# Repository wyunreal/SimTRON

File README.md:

# SimTRON

MultiSim SMS device !

This repo contains source code and hardware specifications for building a 8 SIMs communications device to monitor SMS reception on up to 8 mobile lines.

# Hardware

The device is based on an Arduino PRO mini, running at 16 MHz and 5V. Board designed using Eagle Cad, sources under **hardware** folder.

## Schematic:

## Board:

## Connections:

- **PSW:** power switch, connect the ATX power switch.
- **RSW:** reset switch, connect the ATX reset switch.
- **ATXE:** ATX enable signal, connect, from left to right: ATX Black (GND), ATX Green (Enable)
- **LPWR:** Logic power: connect, from left to right: ATX Purple (5V SB), ATX Black (GND)
- **GSMPWR:** GSM modules [1 to 4] power: connect, from left to right: ATX Red (5V), ATX Black (GND)
- **GSMPWR2:** GSM modules [5 to 8] power: connect, from left to right: Any alternative 5V poser supply (can be ATX Yellow (12V) through a 5V DC-DC step down, ATX Black (GND)
-- Take into account that you don't need to connect this power connector if you closes the JP1 jumper. In this case, all GSM modules will be powered through GSMPWR connector.
- **GSM[1..8]:** gsm modules, take into account polarity, reset pin on GSM module marked as 7 in board.

## List of materials

| Name | link | Unit price | Quantity | Total price |
|------|------|------------|----------|-------------|
| IC 74HC4051 | https://www.amazon.es/cd74hc4051e-Analog-Channel-CKT-16-Ti/dp/B01JV6VPJ8/ref=sr_1_fkmr1_1?ie=UTF8&qid=1528913467&sr=8-1-fkmr1&keywords=analog+mux+4051 | 3.50 € | 1 | 3.50 € |
| GPRS SIm800L Modem | https://www.amazon.es/Sharplace-SIM800L-Tarjeta-Cuatribanda-QUAD-BAND/dp/B075D9ZYPW/ref=sr_1_16?ie=UTF8&qid=1528789781&sr=8-16&keywords=sim800l | 12.99 € | 8 | 103.92 € |
| Arduino Pro Mini 328P | https://www.amazon.es/Arduino-ATMEGA328-Avr328P-desarrollo-development/dp/B01DLPAAAK/ref=sr_1_2?ie=UTF8&qid=1528790069&sr=8-2&keywords=arduino+pro+mini | 5 € | 1 | 5 € |
| FTDI USB Adapter | https://www.amazon.es/tinxi%C2%AE-FT232RL-adaptador-convertidor-Arduino/dp/B01C2P9GD2/ref=sr_1_8?s=electronics&ie=UTF8&qid=1528790180&sr=1-8&keywords=ftdi+usb | 5.99 € | 1 | 5.99 € |
| Mini USB to Micro USB cable | https://www.amazon.es/Extensi%C3%B3n-Adaptador-Dispositivo-Charger-Converter/dp/B01MEDCEBJ/ref=sr_1_6?s=electronics&ie=UTF8&qid=1528911416&sr=1-6&keywords=mini+usb+to+micro+usb | 7.99 € | 1 | 7.99 € |
| Raspberry PI Zero W Starter kit | https://www.amazon.es/PiHut-Zero-Essentials-Kit-Raspberry/dp/B06XCYGP27/ref=sr_1_5?ie=UTF8&qid=1528790276&sr=8-5&keywords=raspberry+pi+zero+w | 25 € | 1 | 25 € |
| Micro ATX enclosure | https://www.amazon.es/gp/product/B00TKP0E34/ref=oh_aui_detailpage_o01_s00?ie=UTF8&psc=1 | 46.95 € | 1 | 46.95 € |
| Manufactoring at China | https://www.pcbway.com/ | 10 € | 1 | 10 € |

Total price: 208.35 €

## Printed parts

This part has been designed to support the 8 Bnc antennas, fitting in any ATX case back side. You can print it with any 3D printer.

# Firmware

The firmware is under the **firmware** folder, you can use Arduino IDE to mod or add new features.

## Interface

The firmware uses **Serial** interface to communicate with host computer, the commands follows a simple text protocol, one command on each line and with following structure:

`commandOpCode param1 param2 param3`

Commands response are valid JSON objects.

### Available commands:

**Status command:**

`status channelNo`

Param: int, GSM channel number, 0 to 7

Response:

```javascript
{
  "type": "status",
  "channel": int, // the channel: 0 to 7
  "power": "string", // whether the ATX power is "on" or "off"
  "isEnabled": int, // whether the channel is enabled (1) or not (0)
  "icc": "string", // full ICC of the sim, if not sim inserted, empty icc will be returned
  "msisdn": "string", // full msisdn of the sim, if no sim inserted, empty msisdn will be returned, also, if unknown msisd, a question mark will be returned "?"
  "networkStatus": int, // 1 to 10, indicating the GSM network status of the channel
  "status": "string" // descriptive and printable message for networkStatus
}
```

**Catalog command:**

`catalog`

Response:

8 status objects, one per GSM channel (see status command)

**Enable command:**

`enable channelNo`

Param: int, GSM channel number, 0 to 7

Response:

Same response than status command.

**Disable command:**

`disable channelNo`

Param: int, GSM channel number, 0 to 7

Response:

Same response than status command.

**Send SMS command:**

`sendSms channelNo destinationMsisdn "SMS text"`

Params:
- int channelNo: GSM channel number, 0 to 7, this channel will be used as sender.
- string senderMsisdn: MSISDN to send to.
- string smsText: short text to send as SMS (max 130 chars)

Response:

if SMS sent correctly:

```javascript
{
  "type": "info",
  "body": "SMS sent"
}
```

if not:

```javascript
{
  "type": "error",
  "body": "Error sending SMS"
}
```

**Reset command:**

`reset`

Response:

No response, the system will reset and boot messages will be shown.

**Support command:**

`support`

Response:

```javascript
{
  "type": "support",
  "body": "Simtron v1.0.0 get support at https://github.com/wyunreal/simtron"
}
```

## Push messages

The device can send messages to the host computer without the needding of a command, these messages are:

**Boot started:**

```javascript
{
  "type": "booting",
  "body": "Booting Up ..."
}
```

**Boot completed:**

```javascript
{
  "type": "booting",
  "body": "System ready ..."
}
```

**SMS Received:**

```javascript
{
  "type": "sms",
  "channel": int, // the channel: 0 to 7, receiver of the SMS
  "icc": "string", // full ICC of the sim receiving the SMS
  "msisdn": "string", // full msisdn of the sim receiving the SMS, if unknown msisd, a question mark will be returned "?"
  "sender": "string", // sender MSISDN;
  "datetime": "string", // a date and time string, ready for presentation
  "body": "string" // SMS text
}
```

## Burning the firmware to Arduino Pro Mini

As the firmware enables the Watch Dog Timer, in order to being able using an Arduino Pro Mini, you need to burn the Arduino UNO bootloader first, this is completely safe as Arduino Pro Mini is a tiny but full featured version of the Arduino UNO.

Follow these instructions to burn the bootloader using another arduino as programmer:

https://www.luisllamas.es/usar-arduino-para-reprogramar-el-bootloader/

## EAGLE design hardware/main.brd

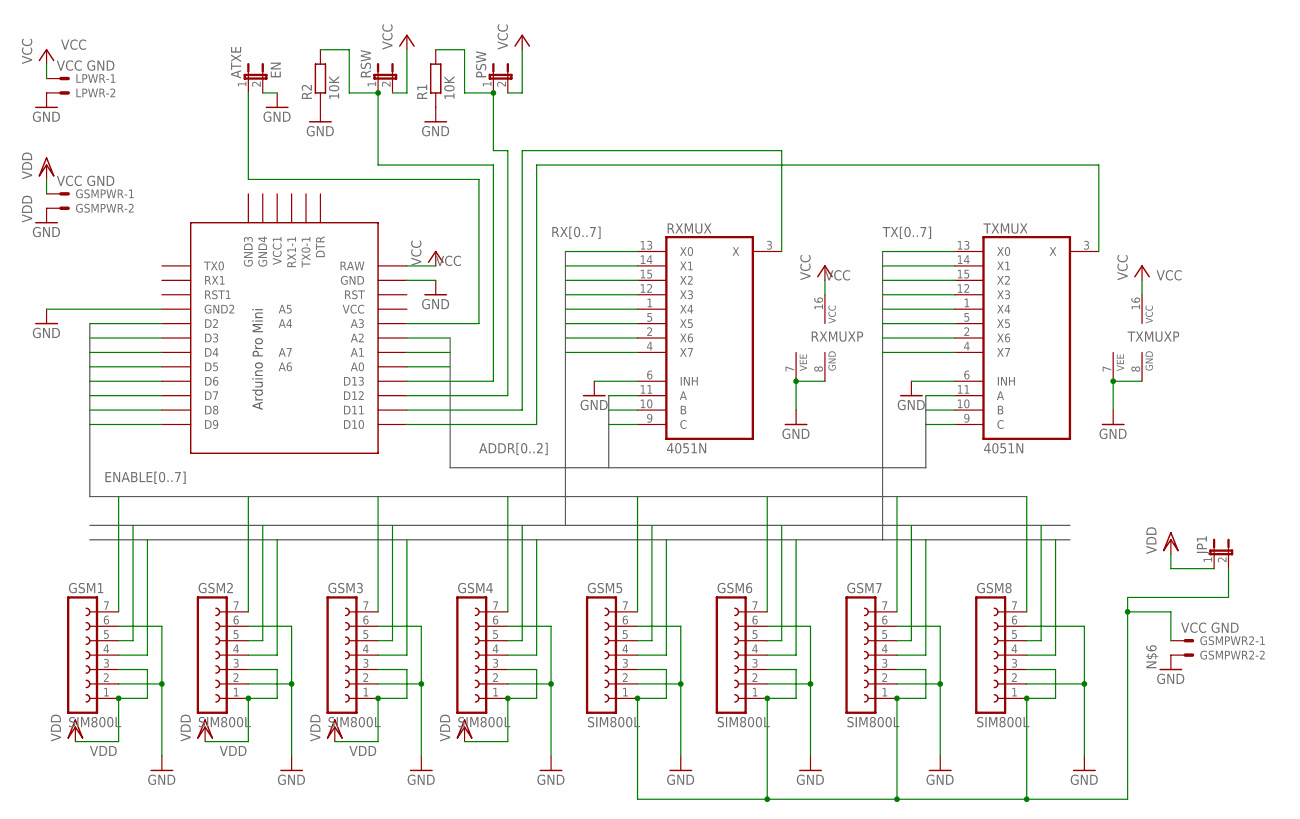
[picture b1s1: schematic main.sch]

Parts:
ARDUINO: PRO-MINI; PRO-MINI-2
ATXE: EN; JP1
GSM1, GSM2, GSM3, GSM4, GSM5, GSM6, GSM7, GSM8: SIM800L; FE07
GSMPWR, GSMPWR2: VCC GND; 22-23-2021
JP1: JP1
LPWR: VCC GND; 22-23-2021
PSW: JP1
R1, R2: 10K; 0204/7
RSW: JP1
RXMUX: 4051N; DIL16
TXMUX: 4051N; DIL16

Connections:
ADDR0: ARDUINO.A2, RXMUX.11 (A), TXMUX.11 (A)
ADDR1: ARDUINO.A1, RXMUX.10 (B), TXMUX.10 (B)
ADDR2: ARDUINO.A0, RXMUX.9 (C), TXMUX.9 (C)
ENABLE0: ARDUINO.D2, GSM1.7
ENABLE1: ARDUINO.D3, GSM2.7
ENABLE2: ARDUINO.D4, GSM3.7
ENABLE3: ARDUINO.D5, GSM4.7
ENABLE4: ARDUINO.D6, GSM5.7
ENABLE5: ARDUINO.D7, GSM6.7
ENABLE6: ARDUINO.D8, GSM7.7
ENABLE7: ARDUINO.D9, GSM8.7
GND: ARDUINO.GND, ARDUINO.GND1 (GND2), ATXE.2, GSM1.2, GSM1.6, GSM2.2, GSM2.6, GSM3.2, GSM3.6, GSM4.2, GSM4.6, GSM5.2, GSM5.6, GSM6.2, GSM6.6, GSM7.2, GSM7.6, GSM8.2, GSM8.6, GSMPWR.2, GSMPWR2.2, LPWR.2, R1.1, R2.1, RXMUX.6 (INH), RXMUX.7 (VEE), RXMUX.8 (GND), TXMUX.6 (INH), TXMUX.7 (VEE), TXMUX.8 (GND)
unnamed: ARDUINO.D11, RXMUX.3 (X)
unnamed: ARDUINO.D10, TXMUX.3 (X)
unnamed: ARDUINO.D13, R2.2, RSW.1
unnamed: GSM5.1, GSM5.3, GSM6.1, GSM6.3, GSM7.1, GSM7.3, GSM8.1, GSM8.3, GSMPWR2.1, JP1.2
unnamed: ARDUINO.A3, ATXE.1
unnamed: ARDUINO.D12, PSW.1, R1.2
RX0: GSM1.5, RXMUX.13 (X0)
RX1: GSM2.5, RXMUX.14 (X1)
RX2: GSM3.5, RXMUX.15 (X2)
RX3: GSM4.5, RXMUX.12 (X3)
RX4: GSM5.5, RXMUX.1 (X4)
RX5: GSM6.5, RXMUX.5 (X5)
RX6: GSM7.5, RXMUX.2 (X6)
RX7: GSM8.5, RXMUX.4 (X7)
TX0: GSM1.4, TXMUX.13 (X0)
TX1: GSM2.4, TXMUX.14 (X1)
TX2: GSM3.4, TXMUX.15 (X2)
TX3: GSM4.4, TXMUX.12 (X3)
TX4: GSM5.4, TXMUX.1 (X4)
TX5: GSM6.4, TXMUX.5 (X5)
TX6: GSM7.4, TXMUX.2 (X6)
TX7: GSM8.4, TXMUX.4 (X7)
VCC: ARDUINO.RAW, LPWR.1, PSW.2, RSW.2, RXMUX.16 (VCC), TXMUX.16 (VCC)
VDD: GSM1.1, GSM1.3, GSM2.1, GSM2.3, GSM3.1, GSM3.3, GSM4.1, GSM4.3, GSMPWR.1, JP1.1

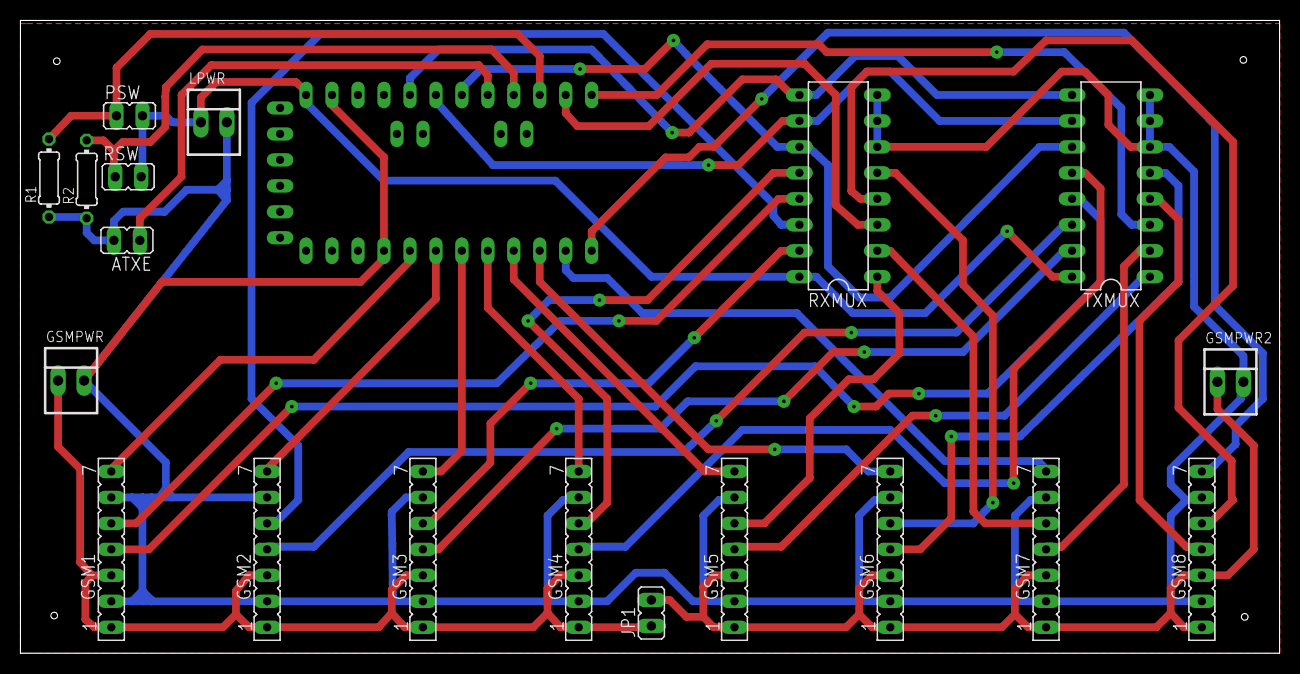
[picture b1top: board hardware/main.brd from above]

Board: 2 copper layers, 123.2 x 61.9 mm, 20 parts (0 on the bottom side), 36 nets.

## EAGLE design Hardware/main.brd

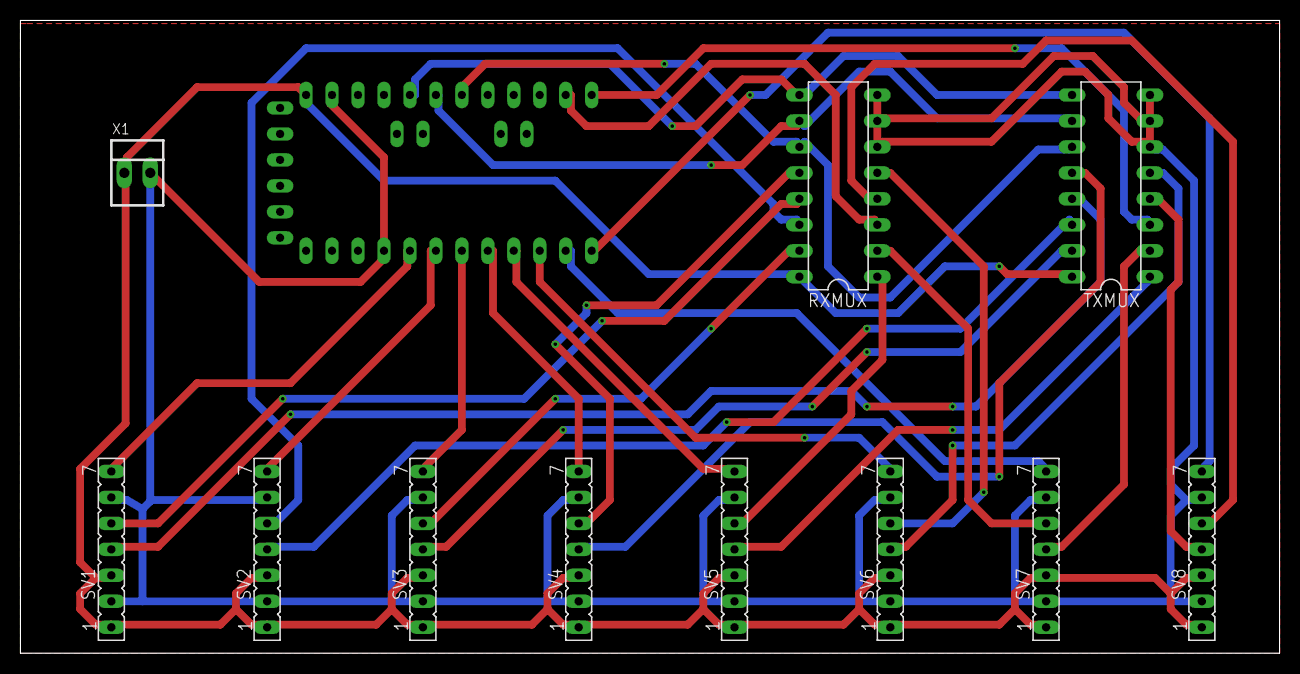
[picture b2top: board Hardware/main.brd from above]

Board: 2 copper layers, 123.2 x 61.9 mm, 12 parts (0 on the bottom side), 32 nets.

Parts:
RXMUX: 4051N; DIL16
SV1, SV2, SV3, SV4, SV5, SV6, SV7, SV8: FE07
TXMUX: 4051N; DIL16
U$1: PRO-MINI-2
X1: 22-23-2021

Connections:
ADDR0: RXMUX.11, TXMUX.11, U$1.A2
ADDR1: RXMUX.10, TXMUX.10, U$1.A1
ADDR2: RXMUX.9, TXMUX.9, U$1.A0
ENABLE0: SV1.7, U$1.D2
ENABLE1: SV2.7, U$1.D3
ENABLE2: SV3.7, U$1.D4
ENABLE3: SV4.7, U$1.D5
ENABLE4: SV5.7, U$1.D6
ENABLE5: SV6.7, U$1.D7
ENABLE6: SV7.7, U$1.D8
ENABLE7: SV8.7, U$1.D9
GND: RXMUX.6, RXMUX.8, SV1.2, SV1.6, SV2.2, SV2.6, SV3.2, SV3.6, SV4.2, SV4.6, SV5.2, SV5.6, SV6.2, SV6.6, SV7.2, SV7.6, SV8.2, SV8.6, TXMUX.6, TXMUX.8, U$1.GND, U$1.GND1, X1.2
unnamed: RXMUX.3, U$1.D11
unnamed: TXMUX.3, U$1.D10
RX0: RXMUX.13, SV1.5
RX1: RXMUX.14, SV2.5
RX2: RXMUX.15, SV3.5
RX3: RXMUX.12, SV4.5
RX4: RXMUX.1, SV5.5
RX5: RXMUX.5, SV6.5
RX6: RXMUX.2, SV7.5
RX7: RXMUX.4, SV8.5
TX0: SV1.4, TXMUX.13
TX1: SV2.4, TXMUX.14
TX2: SV3.4, TXMUX.15
TX3: SV4.4, TXMUX.12
TX4: SV5.4, TXMUX.1
TX5: SV6.4, TXMUX.5
TX6: SV7.4, TXMUX.2
TX7: SV8.4, TXMUX.4
VCC: RXMUX.16, SV1.1, SV1.3, SV2.1, SV2.3, SV3.1, SV3.3, SV4.1, SV4.3, SV5.1, SV5.3, SV6.1, SV6.3, SV7.1, SV7.3, SV8.1, SV8.3, TXMUX.16, U$1.RAW, X1.1
VEE: RXMUX.7, TXMUX.7

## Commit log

2018-02-24 first version of SimTRON firmware
2018-03-01 adding input commands
2018-03-07 adding channel address map
2018-03-09 fixing some json syntax errors
2018-03-11 Adding board design (eagle project)
2018-03-11 moving hardware to new folder
2018-03-11 moving hardware to definitive folder
2018-03-19 new firmware version, also adding support for ICC
2018-03-20 fix couple issues related to ICC parsing
2018-03-21 Adding network status report on status commands
2018-03-21 notifying status change, affecting ICC read and network registration
2018-03-21 implementing catalog command
2018-03-31 some error checking and secure programming on the furmware
2018-03-31 adding some boolean functions toadd semantics to main loop
2018-04-01 Adding msisdn read
2018-04-01 auto status are now marked as statusUpdate
2018-04-01 making status update on demand, removing network status check proactively
2018-04-03 fixing catalog command
2018-05-27 doing some fixes on the hardware, increasing vias size and removing DRC errors
2018-05-31 removing lot of warnings and enabling WDT
2018-05-31 adding reset command and sendSMS command
2018-05-31 adding support command
2018-06-01 some minor fixes
2018-06-16 adding ATX control electronics
2018-06-17 adding power management to arduino sketch
2018-06-17 adding extra power supply for GSM, and connecting to gsm power through a jumper
2018-06-17 moving around hard
2018-06-17 fixing case issue in hardware folder
2018-06-17 adding printed atx case parts
2018-06-17 adding preview of atx backpannel part
